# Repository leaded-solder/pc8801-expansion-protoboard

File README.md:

# NEC PC-8801 expansion protoboard
This board is meant to be a prototyping board for creating expansion cards for the NEC PC-8801 series of Japanese-market personal computers. It is intended to be a substitute for the Sunhayato MCC-151 prototyping board, which is (as far as I know) no longer available for purchase.

This board was developed as part of a [leaded solder](https://www.leadedsolder.com) web log entry. If it saved you some time or money, [please consider backing the site on Patreon](https://www.patreon.com/leadedsolder).

## Bill of Materials (Optional)
The card itself is enough for most users, but you may wish to add a card ejector in order to make it easier to insert and remove the card while you are prototyping your circuit. The 8801 _really_ gets a death grip on those cards.

I have tested fitment with the common and still-available Bivar CP-26 series ejector, so I suggest buying that. Installing the roll pins for the ejector lever is somewhat challenging for me, so I would appreciate any advice on how to make it faster and more consistent!

## Version History
### v0.3
 - Fixed the problem with the PC-8801 edge footprint where the "B" side pins were on the bottom ("A" side) and the "A" side pins were on the top ("B" side.) As you might expect, this kept things from working!

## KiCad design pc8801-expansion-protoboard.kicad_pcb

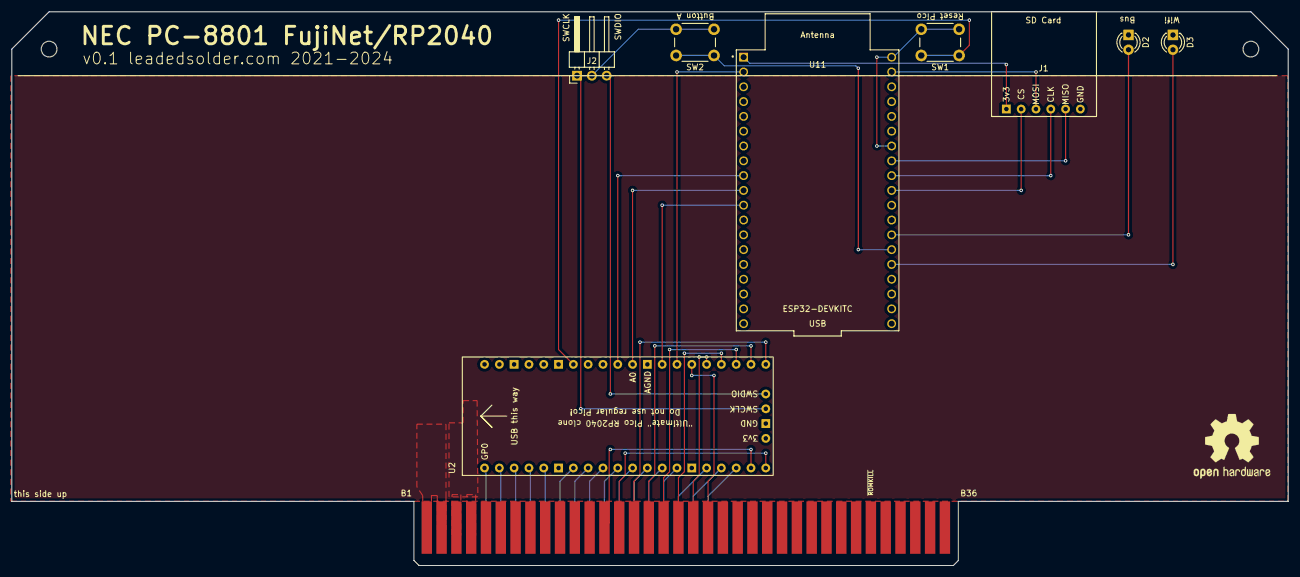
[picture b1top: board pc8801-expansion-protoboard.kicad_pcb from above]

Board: 2 copper layers, 219.0 x 95.0 mm, 9 parts (0 on the bottom side), 42 nets.

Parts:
D2: Bus LED; LED_D3.0mm
D3: Wifi LED; LED_D3.0mm
J1: SD card; microSD_AliExpress
J2: Debug (Pico Probe); PinHeader_1x03_P2.54mm_Horizontal
SW1: Reset Pico; SW_PUSH_6mm
SW2: Button A; SW_PUSH_6mm
U1: ExpansionEdge; PC88 Edge
U2: Ultimate_Pico_RP2040
U11: ESP32-DEVKITC; MODULE_ESP32-DEVKITC

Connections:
+5V: U1.3A (+5V), U1.4A (+5V)
/AB0: U1.5A (AB0), U2.1 (GPIO_0)
/AB1: U1.6A (AB1), U2.2 (GPIO_1)
/AB2: U1.7A (AB2), U2.3 (GPIO_2)
/AB3: U1.8A (AB3), U2.4 (GPIO_3)
/AB4: U1.9A (AB4), U2.5 (GPIO_4)
/AB5: U1.10A (AB5), U2.7 (GPIO_5)
/AB6: U1.11A (AB6), U2.8 (GPIO_6)
/AB7: U1.12A (AB7), U2.9 (GPIO_7)
/AB8: U1.13A (AB8), U2.10 (GPIO_8)
/AB9: U1.14A (AB9), U2.11 (GPIO_9)
/AB10: U1.15A (AB10), U2.12 (GPIO_10)
/AB11: U1.16A (AB11), U2.13 (GPIO_11)
/AB12: U1.17A (AB12), U2.14 (GPIO_12)
/AB13: U1.18A (AB13), U2.16 (GPIO_13)
/AB14: U1.19A (AB14), U2.17 (GPIO_14)
/AB15: U1.20A (AB15), U2.18 (GPIO_15)
/BUS_LED: D2.2 (A), U11.26 (IO4)
/CMD: U2.31 (GPIO_A1), U11.9 (IO25)
/DB0: U1.13B (DB0), U2.19 (GPIO_16)
/DB1: U1.14B (DB1), U2.20 (GPIO_17)
/DB2: U1.15B (DB2), U2.21 (GPIO_18)
/DB3: U1.16B (DB3), U2.22 (GPIO_19)
/DB4: U1.17B (DB4), U2.23 (GPIO_20)
/DB5: U1.18B (DB5), U2.24 (GPIO_21)
/DB6: U1.19B (DB6), U2.25 (GPIO_22)
/DB7: U1.20B (DB7), U2.26 (GPIO_23)
/ESP_3v3: J1.1, U11.1 (3V3)
/INT: U2.28 (GPIO_25), U11.11 (IO27)
/PC88_5V: U1.3B (+5V), U1.4B (+5V)
/PICO_SWCLK: J2.1, U2.B3 (SWCLK)
/PICO_SWDIO: J2.3, U2.B4 (SWDIO)
/PROC: U2.30 (GPIO_A0), U11.10 (IO26)
/SPI_CLK: J1.4, U11.30 (IO18)
/SPI_MISO: J1.5, U11.31 (IO19)
/SPI_MOSI: J1.3, U11.37 (IO23)
/WIFI_LED: D3.2 (A), U11.24 (IO2)
/io0: SW2.1, U11.25 (IO0)
/~ESP_RESET: U2.27 (GPIO_24), U11.2 (EN)
/~PICO_RESET: SW1.1, U2.34 (RUN)
/~SPI_CS: J1.2, U11.29 (IO5)
GND: J1.6, J2.2, SW1.2, SW2.2, U1.1A (GND), U1.1B (GND), U1.2A (GND), U1.2B (GND), U2.6 (GND), U2.15 (GND), U2.29 (AGND), U2.35 (GND), U2.38 (GND), U2.B2 (GND), U11.14 (GND1), U11.32 (GND2), U11.38 (GND3)

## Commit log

2021-12-16 Pinout table
2021-12-20 Use compatible notation, overbar is broken
2021-12-20 Symbol and schematic
2021-12-20 Tying power nets together
2021-12-20 Some progress
2021-12-20 Minor silk prep
2021-12-20 Power bars
2021-12-20 Power rails, of a sort
2021-12-25 Here goes nothing
2021-12-26 need to fix edge cut
2021-12-30 Edge brought over to get closer to SB-II clone
2022-01-11 ejector holes
2022-01-11 little baby edge chamfer
2022-01-11 Unnecessary logo
2022-01-17 Bump copyright date
2022-01-30 Images and README
2022-01-31 Ejector notes
2022-02-01 Move pours around to help avoid rubbing on the ejectors
2022-05-30 Flip-flops and SPI clocks added
2022-05-30 Input SR
2022-05-30 Everything except for the ESP32
2022-05-30 Fix input errors
2022-06-28 Start of a DevKitC footprint
2022-06-28 ESP32 on board
2022-06-28 Begin microSD work
2022-06-28 TF + 3v3 LDO mounted
2022-08-31 Bad FujiNet
2022-08-31 Fix swapped-side near disaster
2022-08-31 Rewire and add test points
2022-09-11 V0.2 for FujiNet sent to JLCPCB
2022-09-11 Fix flipped edge
2022-09-11 Readme fix
2022-09-11 Add ref for card ejector
2022-09-16 Fix too-tiny R1
2022-09-17 Bump version
2022-09-27 reset button
2022-09-28 Add bypass caps for counter and ESP
2022-09-28 Fix up DRC
2022-09-28 Wire ESP32 to system reset
2022-09-29 As per Collapse, jumper-able clocks
2022-09-29 Jumper to disable PU/PD
2022-10-01 Test hooks for SPI clock
2022-10-10 Series 220uF on 5V
2022-10-10 Revise cap placement
2023-05-23 Upgrade to KiCad 7, remove old files
2023-10-31 Fix symbol problem
2023-10-31 Reflow pours
2024-04-06 Ignore lock files
2024-07-06 Place RP2040
2024-07-09 Mocking out Mozzwald's design
2024-07-09 LEDs
2024-07-09 Add Button A
2024-07-09 Throwing stuff at the wall
